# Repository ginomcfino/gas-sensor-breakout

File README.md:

# Gas Sensor Breakout

A PIC16F18344-based gas-sensor board design combining SCD40 CO2 sensing, LuminOX oxygen sensing, CCS811 air-quality sensing, protected power input, and programming and expansion headers.

**Status:** CAD design study; not yet fabricated or bench-tested. ERC, DRC, and schematic-to-board checks report zero findings in KiCad 10.0.5 under the saved project rules.

This is my manually developed circuit and PCB design. Component libraries, manufacturer models, and other supplied assets retain their original attribution.

- [Hardware source](hardware/): hierarchical schematics, PCB, and project settings.
- [Schematic PDF](exports/schematic.pdf) and [component list](exports/bom.csv).
- [Visual guide](docs/README.md): labeled board and schematic views.
- [Check notes](docs/checks/README.md): automated-check results and circuit notes.

Open `hardware/gas-sensor-breakout.kicad_pro` with KiCad 10 and its standard symbol, footprint, and 3D model libraries.

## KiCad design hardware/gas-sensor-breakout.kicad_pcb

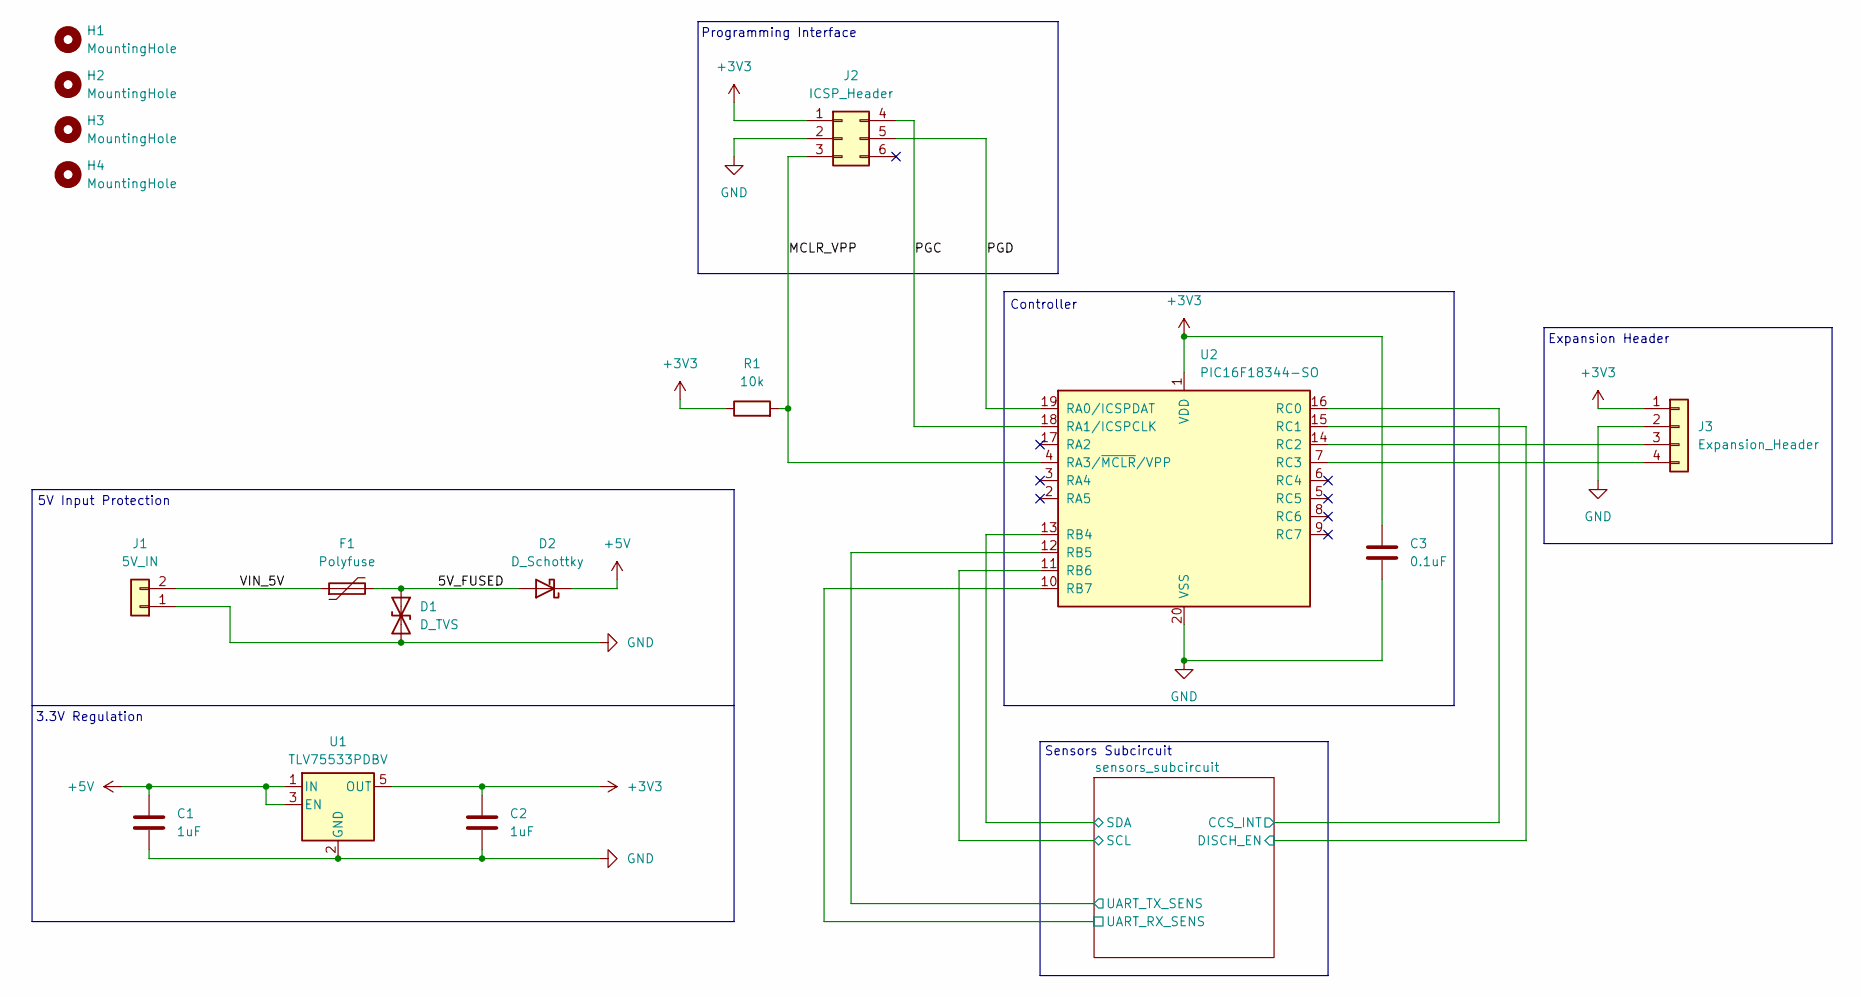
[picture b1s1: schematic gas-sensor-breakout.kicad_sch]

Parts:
C1, C2: 1uF; C_0603_1608Metric
C3: 0.1uF; C_0603_1608Metric
D1: D_TVS; D_SOD-323
D2: D_Schottky; D_SOD-323
F1: Polyfuse; Fuse_1206_3216Metric
H1, H2, H3, H4: MountingHole; MountingHole_3.2mm_M3
J1: 5V_IN; JST_PH_B2B-PH-K_1x02_P2.00mm_Vertical
J2: ICSP_Header; PinHeader_2x03_P2.54mm_Vertical
J3: Expansion_Header; PinHeader_1x04_P2.54mm_Vertical
R1: 10k; R_0603_1608Metric
U1: TLV75533PDBV; SOT-23-5
U2: PIC16F18344-SO; SOIC-20W_7.5x12.8mm_P1.27mm

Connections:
+3V3: C2.1, C3.1, J2.1, J3.1, R1.1, U1.5 (OUT), U2.1 (VDD); also elsewhere on the board
+5V: C1.1, D2.1 (K), U1.1 (IN), U1.3 (EN); also elsewhere on the board
/5V_FUSED: D1.1 (A1), D2.2 (A), F1.2
/MCLR_VPP: J2.3, R1.2, U2.4 (RA3/~MCLR/VPP)
/PGC: J2.4, U2.18 (RA1/ICSPCLK)
/PGD: J2.5, U2.19 (RA0/ICSPDAT)
/VIN_5V: F1.1, J1.2
/sensors_subcircuit/CCS_INT: U2.16 (RC0); also elsewhere on the board
/sensors_subcircuit/DISCH_EN: U2.15 (RC1); also elsewhere on the board
/sensors_subcircuit/SCL: U2.11 (RB6); also elsewhere on the board
/sensors_subcircuit/SDA: U2.13 (RB4); also elsewhere on the board
/sensors_subcircuit/UART_RX_SENS: U2.10 (RB7); also elsewhere on the board
/sensors_subcircuit/UART_TX_SENS: U2.12 (RB5); also elsewhere on the board
GND: C1.2, C2.2, C3.2, D1.2 (A2), J1.1, J2.2, J3.2, U1.2 (GND), U2.20 (VSS); also elsewhere on the board
unnamed: J3.3, U2.14 (RC2)
unnamed: J3.4, U2.7 (RC3)

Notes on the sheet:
Sensors Subcircuit
5V Input Protection
3.3V Regulation
Expansion Header
Controller
Programming Interface

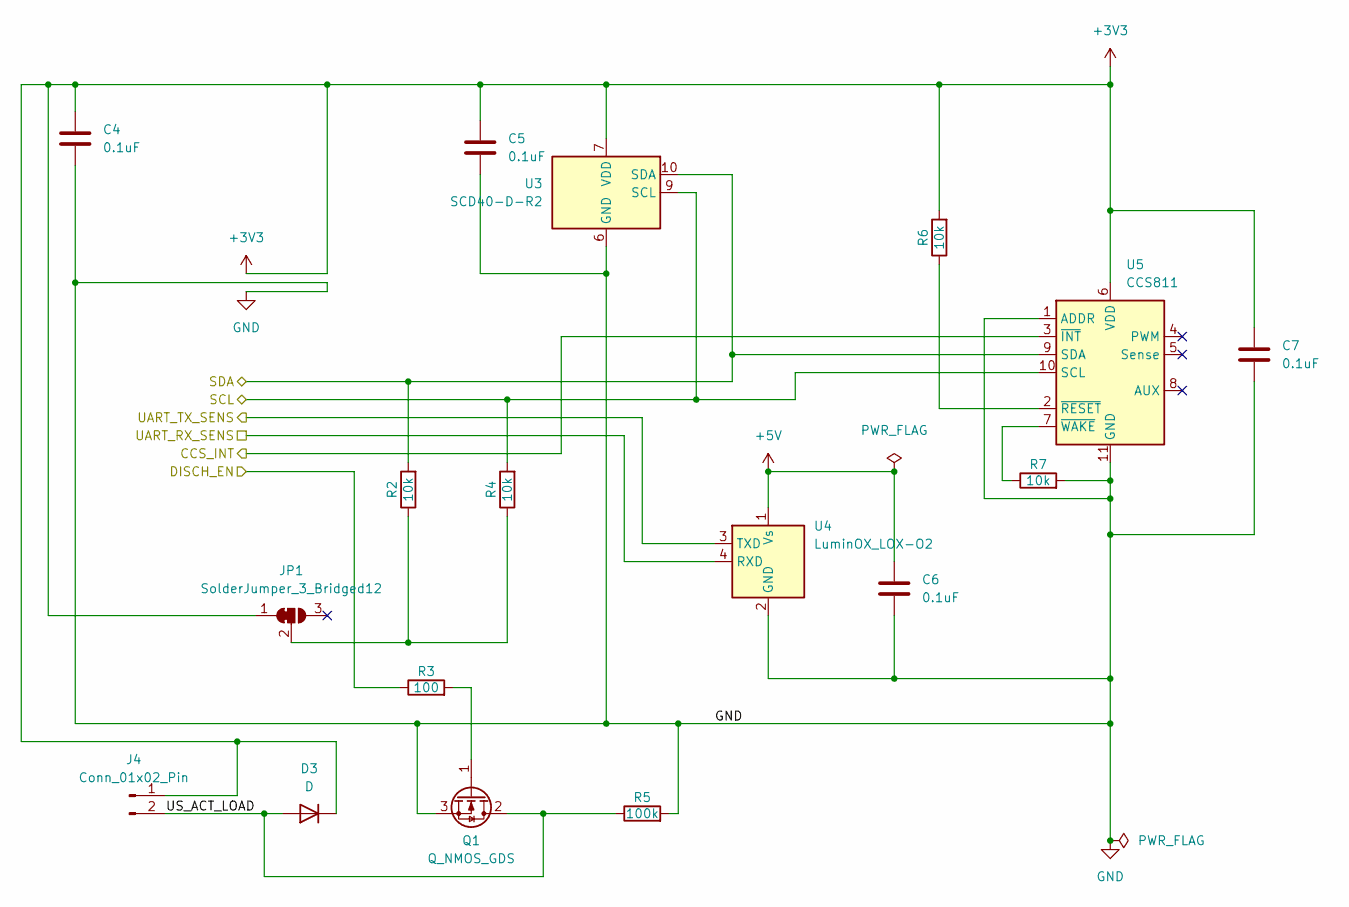
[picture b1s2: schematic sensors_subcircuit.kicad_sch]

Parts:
C4, C5, C6, C7: 0.1uF; C_0603_1608Metric
D3: D; D_SOD-323
J4: Conn_01x02_Pin; PinHeader_1x02_P2.54mm_Vertical
JP1: SolderJumper_3_Bridged12; SolderJumper-3_P1.3mm_Bridged12_Pad1.0x1.5mm
Q1: Q_NMOS_GDS; SOT-23
R2, R4, R6, R7: 10k; R_0603_1608Metric
R3: 100; R_0603_1608Metric
R5: 100k; R_0603_1608Metric
U3: SCD40-D-R2; Sensirion_SCD4x-1EP_10.1x10.1mm_P1.25mm_EP4.8x4.8mm
U4: LuminOX_LOX-O2
U5: CCS811; AMS_LGA-10-1EP_2.7x4mm_P0.6mm

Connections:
+3V3: C4.1, C5.1, C7.1, D3.1 (K), J4.1, JP1.1 (A), R6.2, U3.7 (VDD), U3.19 (VDD), U5.6 (VDD); also elsewhere on the board
+5V: C6.1, U4.1 (Vs); also elsewhere on the board
/sensors_subcircuit/CCS_INT: U5.3 (~INT); also elsewhere on the board
/sensors_subcircuit/DISCH_EN: R3.1; also elsewhere on the board
/sensors_subcircuit/SCL: R4.2, U3.9 (SCL), U5.10 (SCL); also elsewhere on the board
/sensors_subcircuit/SDA: R2.2, U3.10 (SDA), U5.9 (SDA); also elsewhere on the board
/sensors_subcircuit/UART_RX_SENS: U4.4 (RXD); also elsewhere on the board
/sensors_subcircuit/UART_TX_SENS: U4.3 (TXD); also elsewhere on the board
/sensors_subcircuit/US_ACT_LOAD: D3.2 (A), J4.2, Q1.2 (D), R5.1
GND: C4.2, C5.2, C6.2, C7.2, Q1.3 (S), R5.2, R7.2, U3.6 (GND), U3.20 (GND), U3.21 (GND), U4.2 (GND), U5.1 (ADDR), U5.11 (GND); also elsewhere on the board
unnamed: JP1.2 (C), R2.1, R4.1
unnamed: Q1.1 (G), R3.2
unnamed: R6.1, U5.2 (~RESET)
unnamed: R7.1, U5.7 (~WAKE)

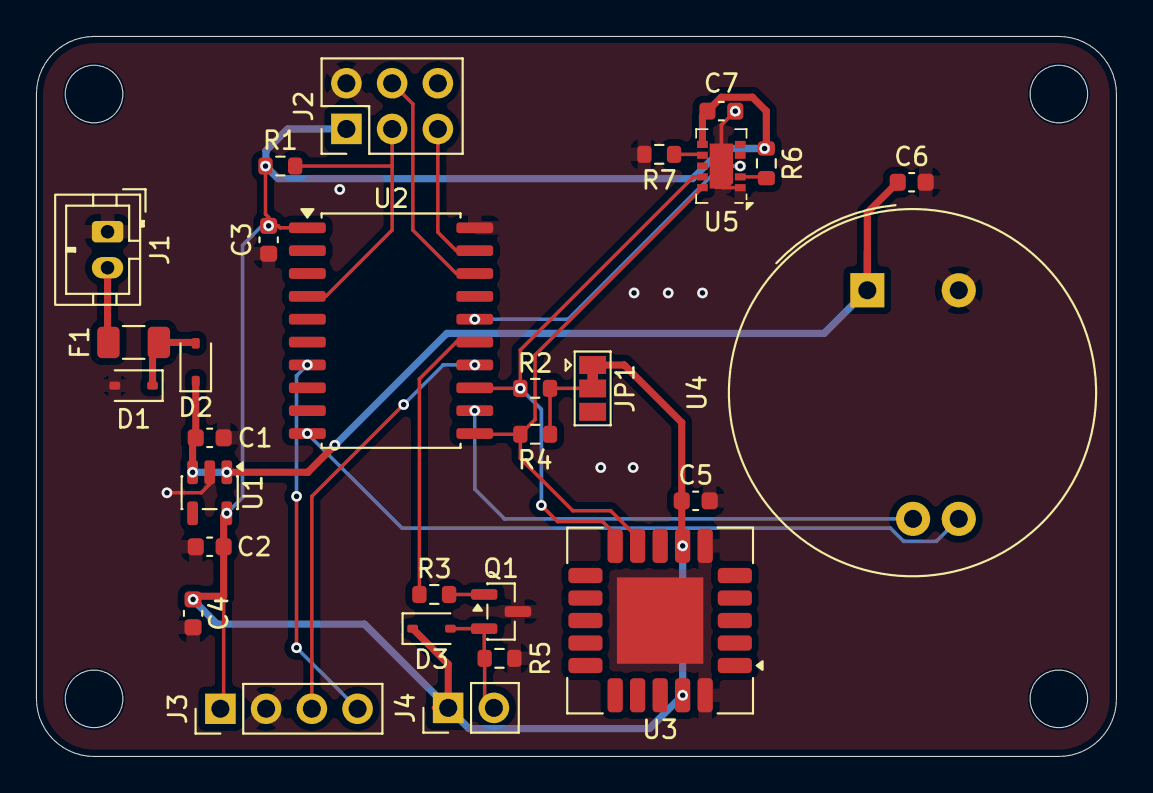
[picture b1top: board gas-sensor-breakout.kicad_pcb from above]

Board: 2 copper layers, 60.0 x 40.0 mm, 33 parts (0 on the bottom side), 21 nets.

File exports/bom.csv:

"Refs","Value","Footprint","Qty","DNP"
"C1","1uF","Capacitor_SMD:C_0603_1608Metric","1",""
"C2","1uF","Capacitor_SMD:C_0603_1608Metric","1",""
"C3","0.1uF","Capacitor_SMD:C_0603_1608Metric","1",""
"C4","0.1uF","Capacitor_SMD:C_0603_1608Metric","1",""
"C5","0.1uF","Capacitor_SMD:C_0603_1608Metric","1",""
"C6","0.1uF","Capacitor_SMD:C_0603_1608Metric","1",""
"C7","0.1uF","Capacitor_SMD:C_0603_1608Metric","1",""
"D1","D_TVS","Diode_SMD:D_SOD-323","1",""
"D2","D_Schottky","Diode_SMD:D_SOD-323","1",""
"D3","D","Diode_SMD:D_SOD-323","1",""
"F1","Polyfuse","Fuse:Fuse_1206_3216Metric","1",""
"J1","5V_IN","Connector_JST:JST_PH_B2B-PH-K_1x02_P2.00mm_Vertical","1",""
"J2","ICSP_Header","Connector_PinHeader_2.54mm:PinHeader_2x03_P2.54mm_Vertical","1",""
"J3","Expansion_Header","Connector_PinHeader_2.54mm:PinHeader_1x04_P2.54mm_Vertical","1",""
"J4","Conn_01x02_Pin","Connector_PinHeader_2.54mm:PinHeader_1x02_P2.54mm_Vertical","1",""
"Q1","Q_NMOS_GDS","Package_TO_SOT_SMD:SOT-23","1",""
"R1","10k","Resistor_SMD:R_0603_1608Metric","1",""
"R2","10k","Resistor_SMD:R_0603_1608Metric","1",""
"R3","100","Resistor_SMD:R_0603_1608Metric","1",""
"R4","10k","Resistor_SMD:R_0603_1608Metric","1",""
"R5","100k","Resistor_SMD:R_0603_1608Metric","1",""
"R6","10k","Resistor_SMD:R_0603_1608Metric","1",""
"R7","10k","Resistor_SMD:R_0603_1608Metric","1",""
"U1","TLV75533PDBV","Package_TO_SOT_SMD:SOT-23-5","1",""
"U2","PIC16F18344-SO","Package_SO:SOIC-20W_7.5x12.8mm_P1.27mm","1",""
"U3","SCD40-D-R2","Sensor:Sensirion_SCD4x-1EP_10.1x10.1mm_P1.25mm_EP4.8x4.8mm","1",""
"U4","LuminOX_LOX-O2","Sensor:LuminOX_LOX-O2","1",""
"U5","CCS811","Package_LGA:AMS_LGA-10-1EP_2.7x4mm_P0.6mm","1",""
